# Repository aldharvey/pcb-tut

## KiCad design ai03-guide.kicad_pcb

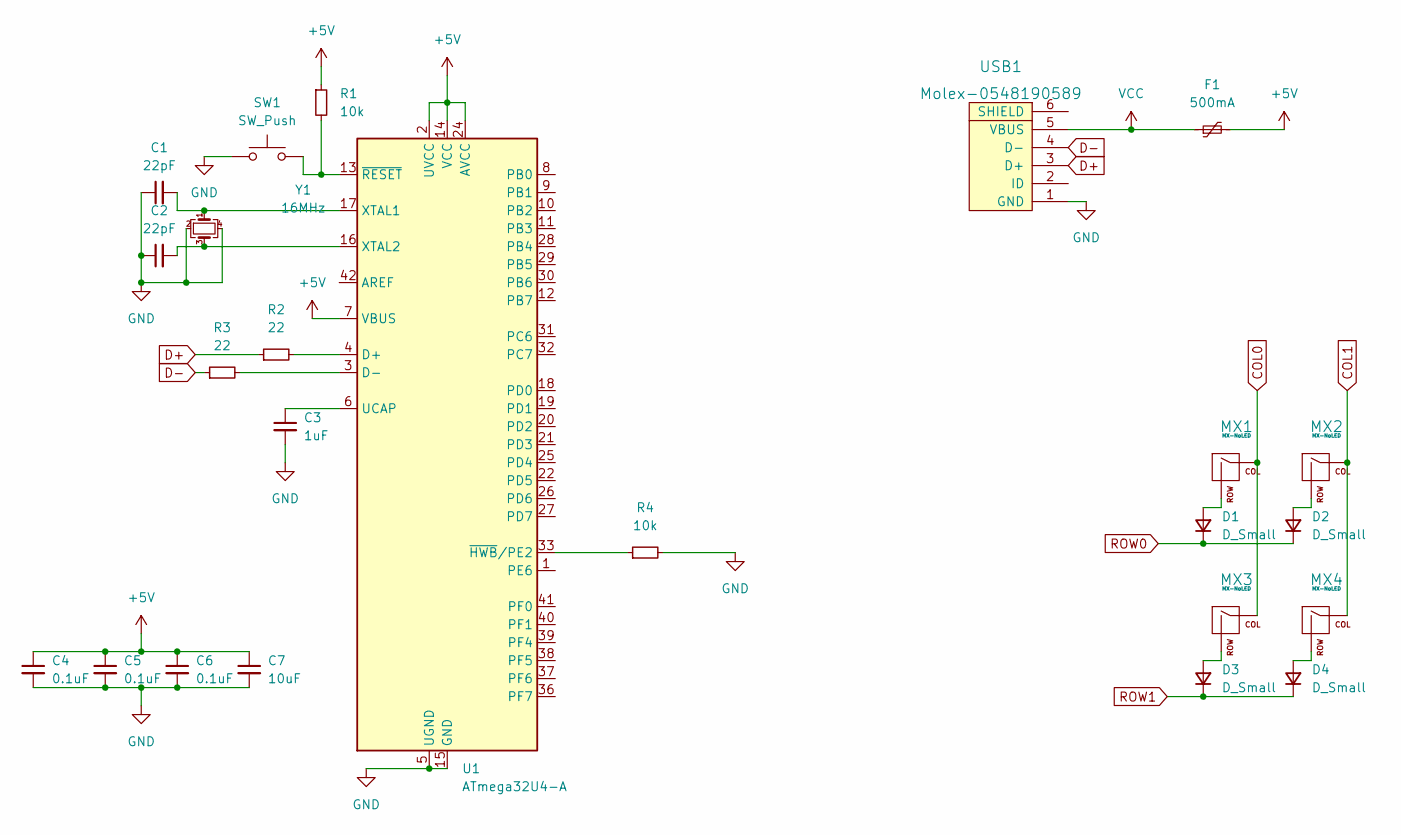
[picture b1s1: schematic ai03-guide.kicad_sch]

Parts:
C1, C2: 22pF; C_0805_2012Metric
C3: 1uF; C_0805_2012Metric
C4, C5, C6: 0.1uF; C_0805_2012Metric
C7: 10uF; C_0805_2012Metric
D1, D2, D3, D4: D_Small; D_SOD-123
F1: 500mA; Fuse_1206_3216Metric
MX1, MX2, MX3, MX4: MX-NoLED; MX-1U-NoLED
R1, R4: 10k; R_0805_2012Metric
R2, R3: 22; R_0805_2012Metric
SW1: SW_Push; SKQG-1155865
U1: ATmega32U4-A; TQFP-44_10x10mm_P0.8mm
USB1: Molex-0548190589
Y1: 16MHz; Crystal_SMD_3225-4Pin_3.2x2.5mm

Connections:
+5V: C4.1, C5.1, C6.1, C7.1, F1.2, R1.1, U1.2 (UVCC), U1.7 (VBUS), U1.14 (VCC), U1.24 (AVCC), U1.34 (VCC), U1.44 (AVCC); also elsewhere on the board
COL0: MX1.1 (COL), MX3.1 (COL); also elsewhere on the board
COL1: MX2.1 (COL), MX4.1 (COL); also elsewhere on the board
D+: R2.1, USB1.3 (D+)
D-: R3.1, USB1.4 (D-)
GND: C1.1, C2.1, C3.2, C4.2, C5.2, C6.2, C7.2, R4.2, SW1.1, U1.5 (UGND), U1.15 (GND), U1.23 (GND), U1.35 (GND), U1.43 (GND), USB1.1 (GND), Y1.2, Y1.4; also elsewhere on the board
unnamed 6: C1.2, U1.17 (XTAL1), Y1.1; also elsewhere on the board
unnamed 7: C2.2, U1.16 (XTAL2), Y1.3; also elsewhere on the board
unnamed 8: C3.1, U1.6 (UCAP); also elsewhere on the board
unnamed: D1.2 (A), MX1.2 (ROW)
unnamed: D2.2 (A), MX2.2 (ROW)
unnamed: D3.2 (A), MX3.2 (ROW)
unnamed: D4.2 (A), MX4.2 (ROW)
unnamed 13: R1.2, SW1.2, U1.13 (~RESET); also elsewhere on the board
unnamed 14: R2.2, U1.4 (D+); also elsewhere on the board
unnamed 15: R3.2, U1.3 (D-); also elsewhere on the board
unnamed 16: R4.1, U1.33 (~HWB/PE2); also elsewhere on the board
ROW0: D1.1 (K), D2.1 (K); also elsewhere on the board
ROW1: D3.1 (K), D4.1 (K); also elsewhere on the board
VCC: F1.1, USB1.5 (VBUS)

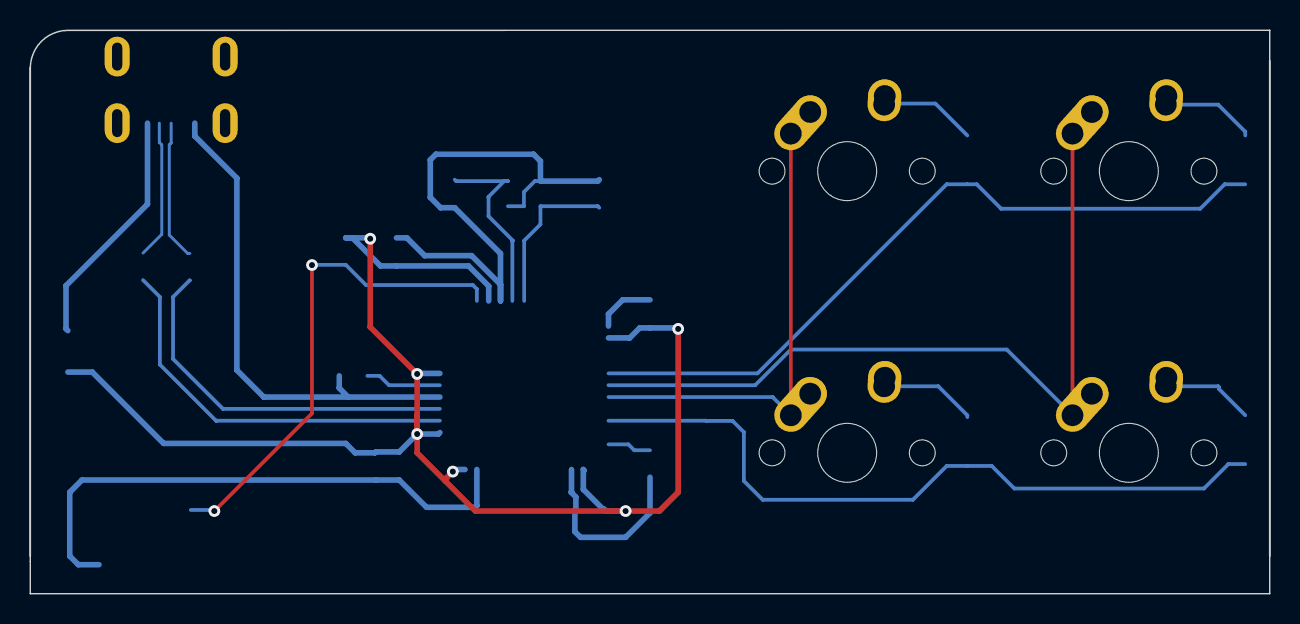
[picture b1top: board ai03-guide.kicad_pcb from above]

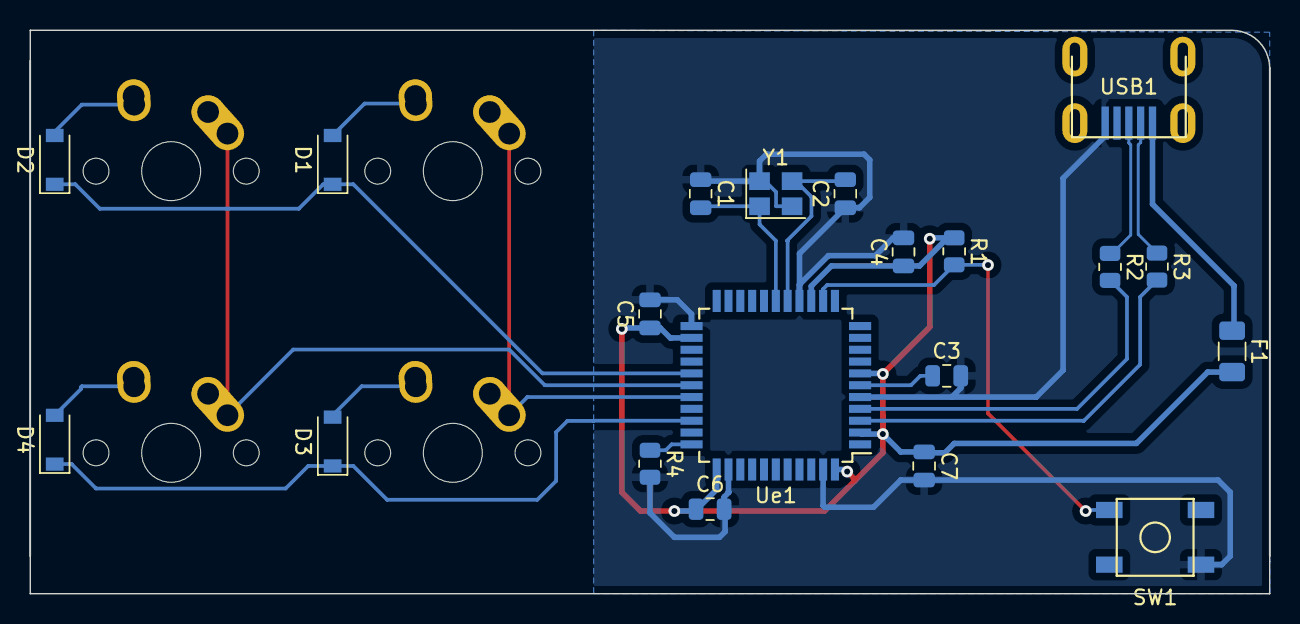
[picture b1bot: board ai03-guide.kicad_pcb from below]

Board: 2 copper layers, 83.8 x 38.1 mm, 24 parts (20 on the bottom side), 20 nets.

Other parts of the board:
Ue1: ATmega32U4-A; TQFP-44_10x10mm_P0.8mm

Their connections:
+5V: Ue1.2 (UVCC), Ue1.7 (VBUS), Ue1.14 (VCC), Ue1.24 (AVCC), Ue1.34 (VCC), Ue1.44 (AVCC); also elsewhere on the board
COL0: Ue1.29 (PB5); also elsewhere on the board
COL1: Ue1.28 (PB4); also elsewhere on the board
GND: Ue1.5 (UGND), Ue1.15 (GND), Ue1.23 (GND), Ue1.35 (GND), Ue1.43 (GND); also elsewhere on the board
unnamed 6: Ue1.17 (XTAL1); also elsewhere on the board
unnamed 7: Ue1.16 (XTAL2); also elsewhere on the board
unnamed 8: Ue1.6 (UCAP); also elsewhere on the board
unnamed 13: Ue1.13 (~RESET); also elsewhere on the board
unnamed 14: Ue1.4 (D+); also elsewhere on the board
unnamed 15: Ue1.3 (D-); also elsewhere on the board
unnamed 16: Ue1.33 (~HWB/PE2); also elsewhere on the board
ROW0: Ue1.27 (PD7); also elsewhere on the board
ROW1: Ue1.31 (PC6); also elsewhere on the board

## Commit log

2022-03-28 Setup
2022-03-28 Add submodules
2022-03-28 Add Libraries
2022-03-29 Footprints
2022-03-30 Prototype Done
